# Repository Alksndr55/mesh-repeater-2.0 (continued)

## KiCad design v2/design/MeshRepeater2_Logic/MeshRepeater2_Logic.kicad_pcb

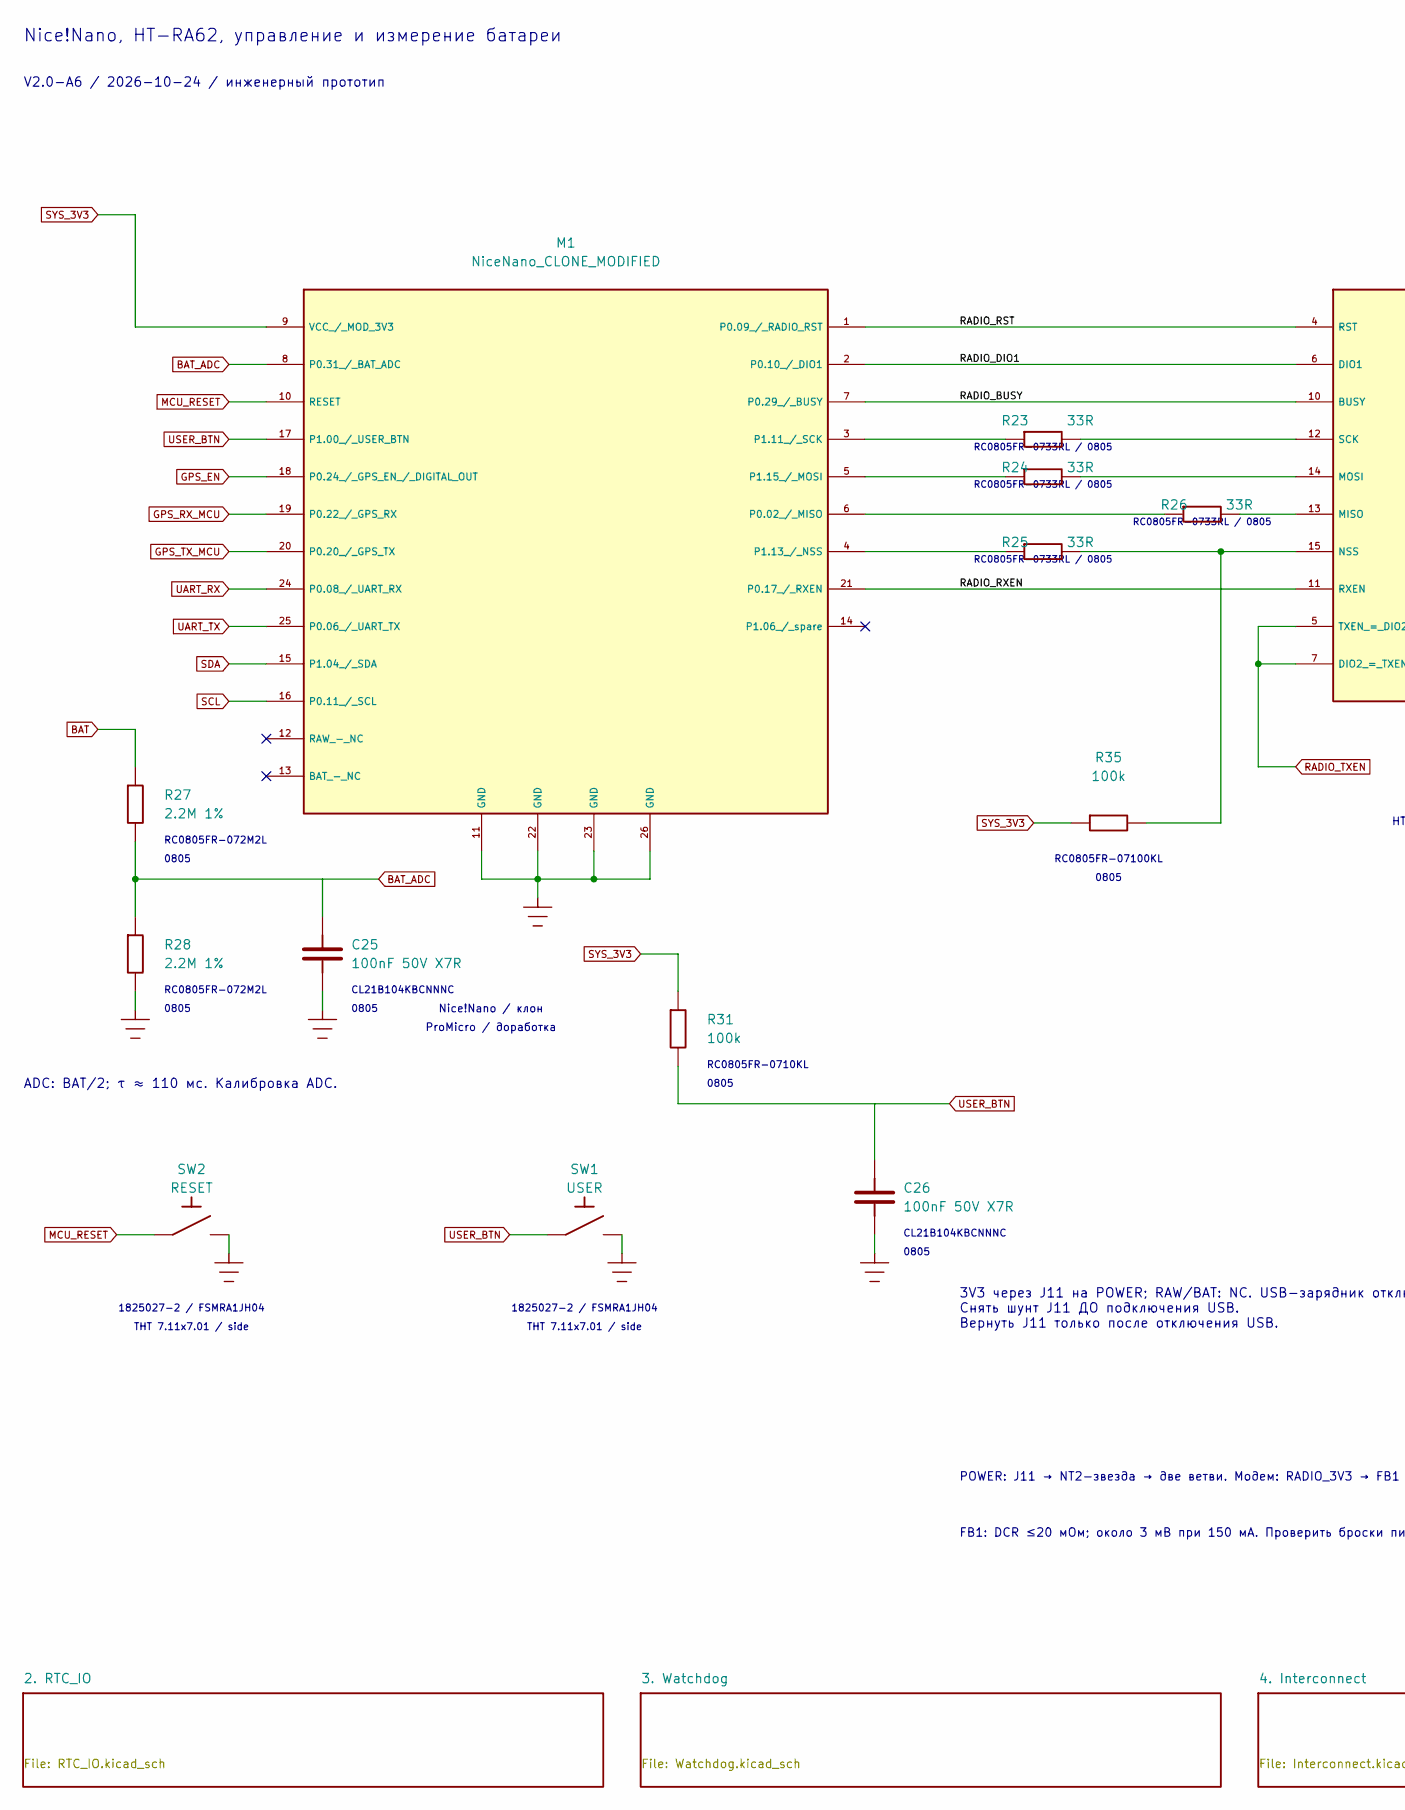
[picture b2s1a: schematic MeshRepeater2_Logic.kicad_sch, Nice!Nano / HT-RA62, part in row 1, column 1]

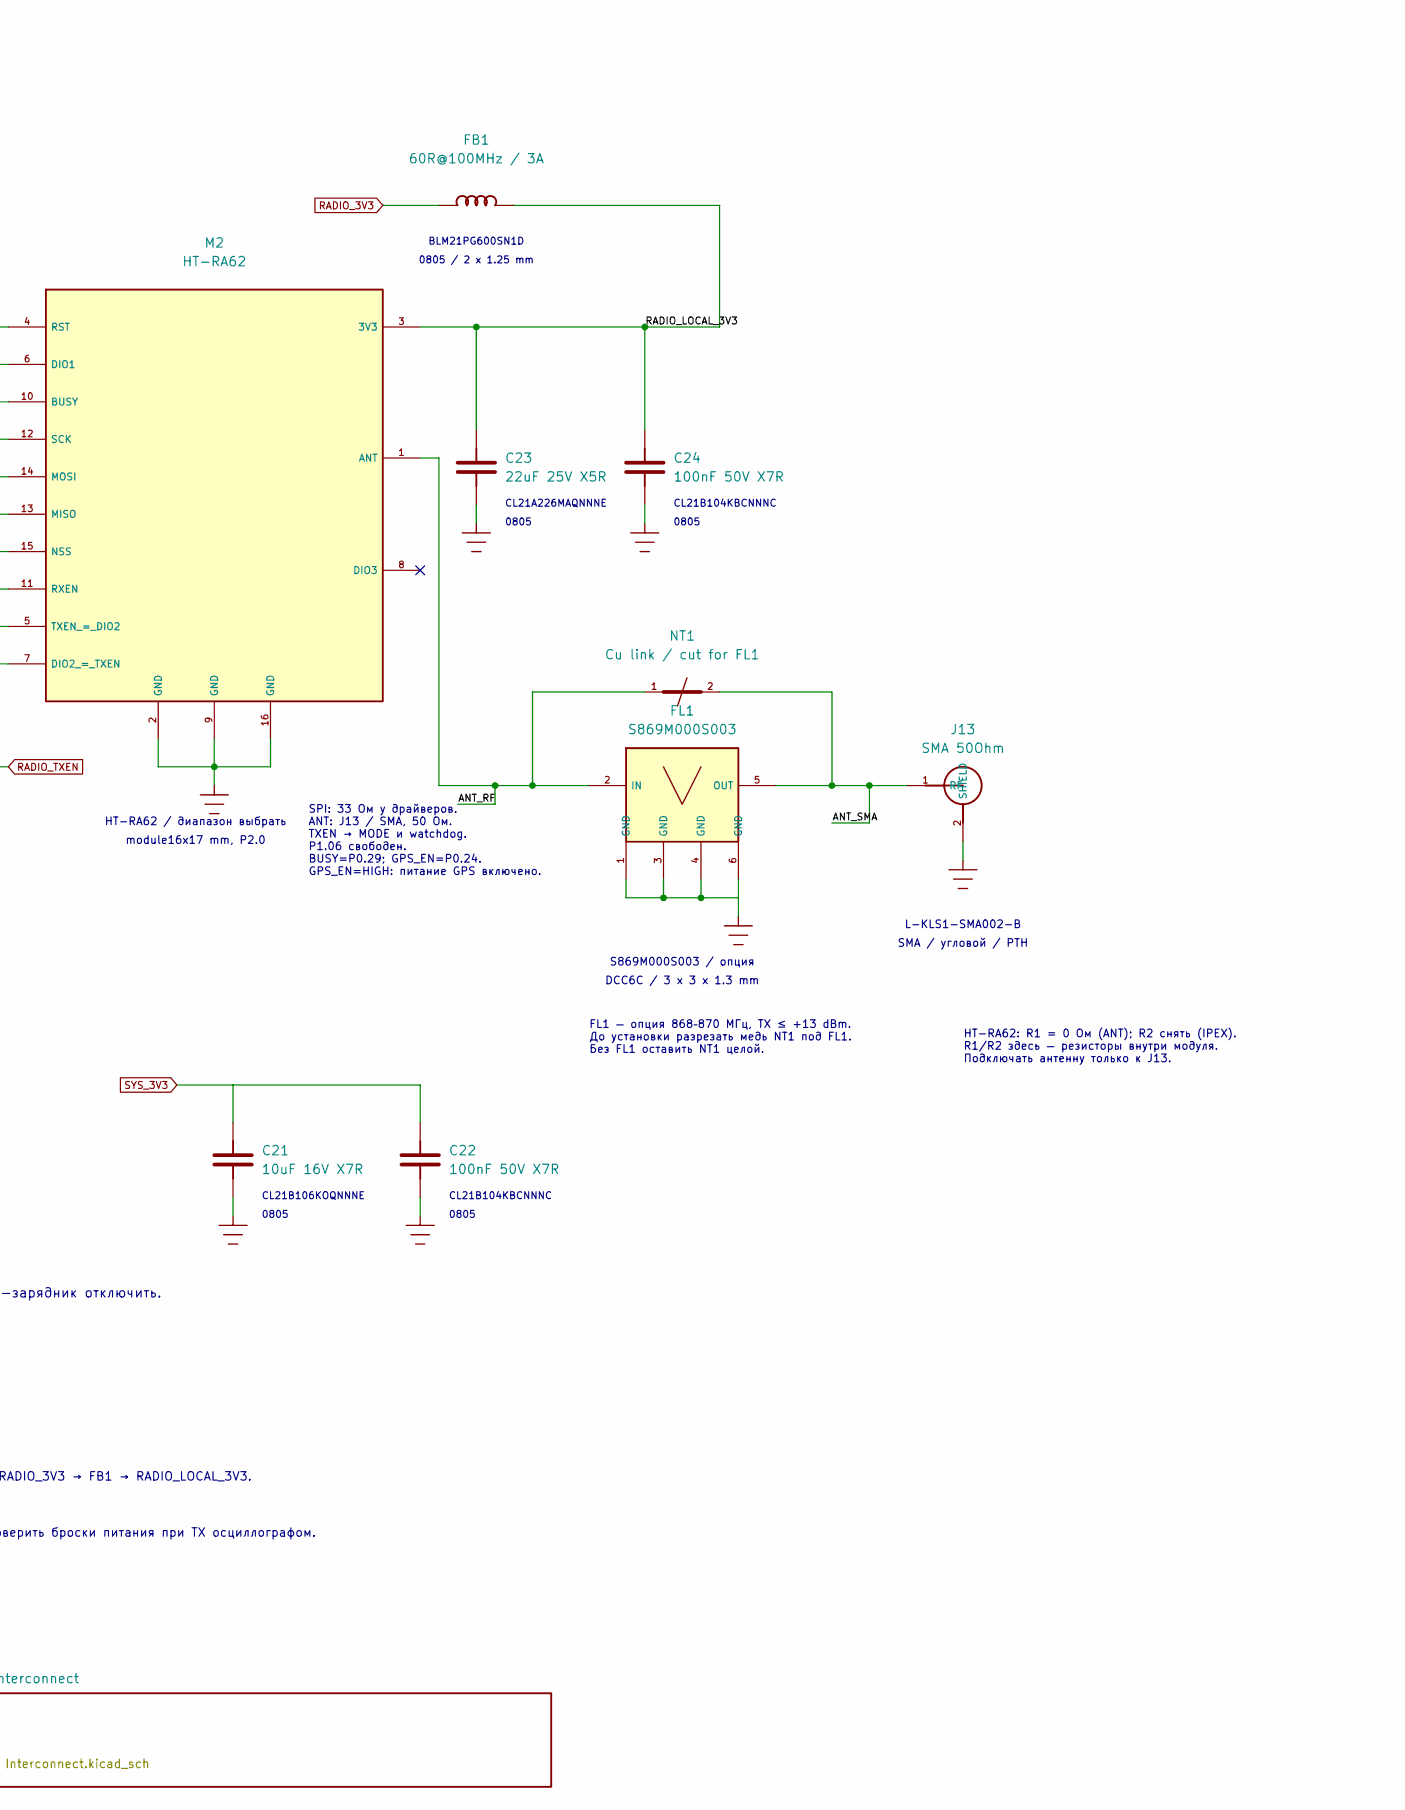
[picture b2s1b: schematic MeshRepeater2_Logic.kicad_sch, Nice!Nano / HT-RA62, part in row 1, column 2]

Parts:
C21: 10uF 16V X7R; C_0805_2012Metric__V2_C21; MPN CL21B106KOQNNNE
C22: 100nF 50V X7R; C_0805_2012Metric__V2_C22; MPN CL21B104KBCNNNC
C23: 22uF 25V X5R; C_0805_2012Metric__V2_C23; MPN CL21A226MAQNNNE
C24: 100nF 50V X7R; C_0805_2012Metric__V2_C24; MPN CL21B104KBCNNNC
C25: 100nF 50V X7R; C_0805_2012Metric__V2_C25; MPN CL21B104KBCNNNC
C26: 100nF 50V X7R; C_0805_2012Metric__V2_C26; MPN CL21B104KBCNNNC
FB1: 60R@100MHz / 3A; Ferrite_Murata_BLM21PG__V2_FB1; MPN BLM21PG600SN1D
FL1: S869M000S003; SAW_AEL_DCC6C_S869M000S003__V2_FL1; MPN S869M000S003
J13: SMA 50Ohm; SMA_KLS1_SMA002_B_Horizontal__V2_J13; MPN L-KLS1-SMA002-B
M1: NiceNano_CLONE_MODIFIED; NiceNano_13x2_Socket__V2_M1; MPN User supplied NiceNano clone
M2: HT-RA62; HT_RA62__V2_M2; MPN HT-RA62 band variant TBD
NT1: Cu link / cut for FL1; RF_Cut_Link_0p6__V2_NT1; MPN PCB copper / not purchased
R23: 33R; R_0805_2012Metric__V2_R23; MPN RC0805FR-0733RL
R24: 33R; R_0805_2012Metric__V2_R24; MPN RC0805FR-0733RL
R25: 33R; R_0805_2012Metric__V2_R25; MPN RC0805FR-0733RL
R26: 33R; R_0805_2012Metric__V2_R26; MPN RC0805FR-0733RL
R27: 2.2M 1%; R_0805_2012Metric__V2_R27; MPN RC0805FR-072M2L
R28: 2.2M 1%; R_0805_2012Metric__V2_R28; MPN RC0805FR-072M2L
R31: 100k; R_0805_2012Metric__V2_R31; MPN RC0805FR-07100KL
R35: 100k; R_0805_2012Metric__V2_R35; MPN RC0805FR-07100KL
SW1: USER; SW_TE_1825027_2_Side__V2_SW1; MPN TE1825027-2 / FSMRA1JH04
SW2: RESET; SW_TE_1825027_2_Side__V2_SW2; MPN TE1825027-2 / FSMRA1JH04

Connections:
/ANT_RF: FL1.2 (IN), M2.1 (ANT), NT1.1 (A)
/ANT_SMA: FL1.5 (OUT), J13.1 (SIGNAL), NT1.2 (B)
/RADIO_BUSY: M1.7 (P0.29_/_BUSY), M2.10 (BUSY_10)
/RADIO_DIO1: M1.2 (P0.10_/_DIO1), M2.6 (DIO1_6)
/RADIO_LOCAL_3V3: C23.1, C24.1, FB1.2, M2.3 (3V3_3)
/RADIO_RST: M1.1 (P0.09_/_RADIO_RST), M2.4 (RST_4)
/RADIO_RXEN: M1.21 (P0.17_/_RXEN), M2.11 (RXEN_11)
BAT: R27.1; also elsewhere on the board
BAT_ADC: C25.1, M1.8 (P0.31_/_BAT_ADC), R27.2, R28.1
GND: C21.2, C22.2, C23.2, C24.2, C25.2, C26.2, FL1.1 (GND), FL1.3 (GND), FL1.4 (GND), FL1.6 (GND), J13.2 (GND), M1.11 (GND), M1.22 (GND), M1.23 (GND), M1.26 (GND), M2.2 (GND_2), M2.9 (GND_9), M2.16 (GND_16), R28.2, SW1.2, SW2.2; also elsewhere on the board
GPS_EN: M1.18 (P0.24_/_GPS_EN_/_DIGITAL_OUT); also elsewhere on the board
GPS_RX_MCU: M1.19 (P0.22_/_GPS_RX); also elsewhere on the board
GPS_TX_MCU: M1.20 (P0.20_/_GPS_TX); also elsewhere on the board
MCU_RESET: M1.10 (RESET), SW2.1; also elsewhere on the board
unnamed: M1.6 (P0.02_/_MISO), R26.2
unnamed: M1.3 (P1.11_/_SCK), R23.1
unnamed: M1.4 (P1.13_/_NSS), R25.1
unnamed: M1.5 (P1.15_/_MOSI), R24.1
unnamed: M2.13 (MISO_13), R26.1
unnamed: M2.14 (MOSI_14), R24.2
unnamed: M2.15 (NSS_15), R25.2, R35.2
unnamed: M2.12 (SCK_12), R23.2
RADIO_3V3: FB1.1; also elsewhere on the board
RADIO_TXEN: M2.5 (TXEN_=_DIO2_5), M2.7 (DIO2_=_TXEN_7); also elsewhere on the board
SCL: M1.16 (P0.11_/_SCL); also elsewhere on the board
SDA: M1.15 (P1.04_/_SDA); also elsewhere on the board
SYS_3V3: C21.1, C22.1, M1.9 (VCC_/_MOD_3V3), R31.1, R35.1; also elsewhere on the board
UART_RX: M1.24 (P0.08_/_UART_RX); also elsewhere on the board
UART_TX: M1.25 (P0.06_/_UART_TX); also elsewhere on the board
USER_BTN: C26.1, M1.17 (P1.00_/_USER_BTN), R31.2, SW1.1

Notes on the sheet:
RC0805FR-0733RL / 0805
CL21B104KBCNNNC
RC0805FR-072M2L
HT-RA62 / диапазон выбрать
0805
CL21B106KOQNNNE
L-KLS1-SMA002-B
DCC6C / 3 x 3 x 1.3 mm
module16x17 mm, P2.0
ADC: BAT/2; τ ≈ 110 мс. Калибровка ADC.
1825027-2 / FSMRA1JH04
HT-RA62: R1 = 0 Ом (ANT); R2 снять (IPEX). R1/R2 здесь — резисторы внутри модуля. Подключать антенну только к J13.
V2.0-A6 / 2026-10-24 / инженерный прототип
FB1: DCR ≤20 мОм; около 3 мВ при 150 мА. Проверить броски питания при TX осциллографом.
0805 / 2 x 1.25 mm
CL21A226MAQNNNE
FL1 — опция 868–870 МГц, TX ≤ +13 dBm. До установки разрезать медь NT1 под FL1. Без FL1 оставить NT1 целой.
POWER: J11 → NT2-звезда → две ветви. Модем: RADIO_3V3 → FB1 → RADIO_LOCAL_3V3.
RC0805FR-0710KL
Nice!Nano, HT-RA62, управление и измерение батареи
ProMicro / доработка
3V3 через J11 на POWER; RAW/BAT: NC. USB-зарядник отключить. Снять шунт J11 ДО подключения USB. Вернуть J11 только после отключения USB.
THT 7.11x7.01 / side
BLM21PG600SN1D
RC0805FR-07100KL
Nice!Nano / клон
SPI: 33 Ом у драйверов. ANT: J13 / SMA, 50 Ом. TXEN → MODE и watchdog. P1.06 свободен. BUSY=P0.29; GPS_EN=P0.24. GPS_EN=HIGH: питание GPS включено.
SMA / угловой / PTH
S869M000S003 / опция

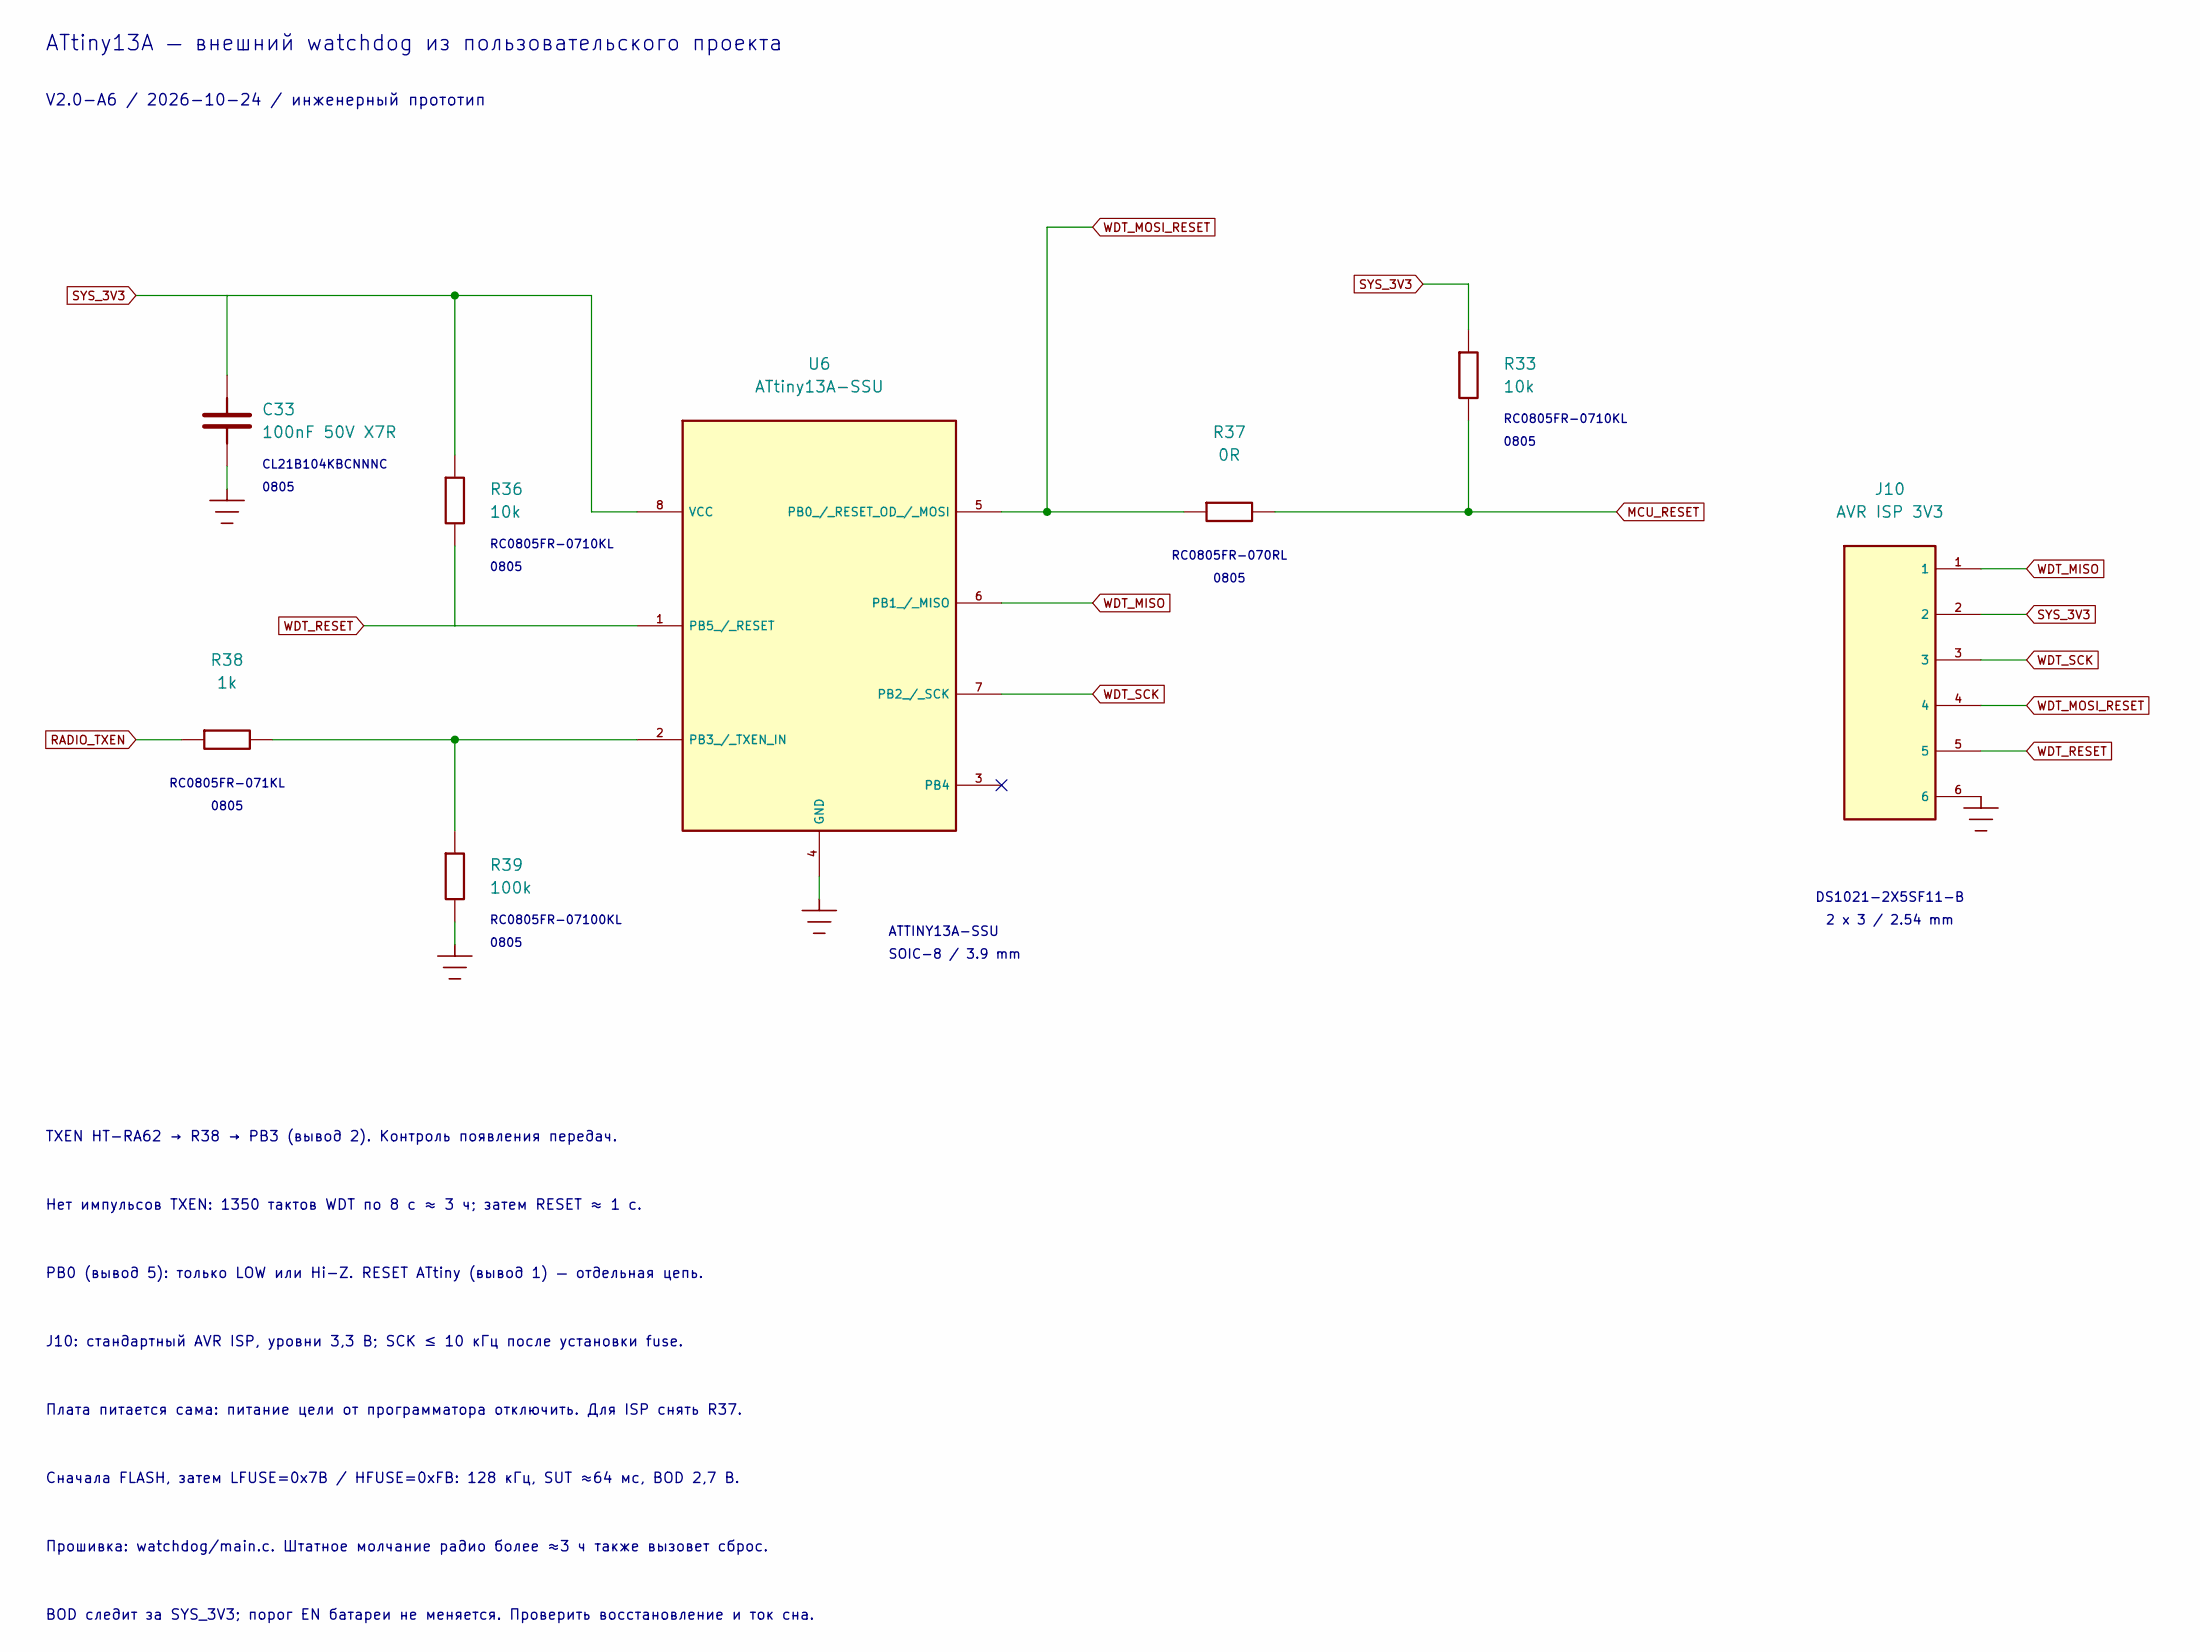
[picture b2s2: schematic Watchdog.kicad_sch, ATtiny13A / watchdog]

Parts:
C33: 100nF 50V X7R; C_0805_2012Metric__V2_C33; MPN CL21B104KBCNNNC
J10: AVR ISP 3V3; PinHeader_2x03_P2.54mm_Vertical__V2_J10; MPN DS1021-2X5SF11-B
R33: 10k; R_0805_2012Metric__V2_R33; MPN RC0805FR-0710KL
R36: 10k; R_0805_2012Metric__V2_R36; MPN RC0805FR-0710KL
R37: 0R; R_0805_2012Metric__V2_R37; MPN RC0805FR-070RL
R38: 1k; R_0805_2012Metric__V2_R38; MPN RC0805FR-071KL
R39: 100k; R_0805_2012Metric__V2_R39; MPN RC0805FR-07100KL
U6: ATtiny13A-SSU; SOIC-8_3.9x4.9mm_P1.27mm__V2_U6; MPN ATTINY13A-SSU

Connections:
GND: C33.2, J10.6, R39.2, U6.4 (GND); also elsewhere on the board
MCU_RESET: R33.2, R37.2; also elsewhere on the board
unnamed: R38.2, R39.1, U6.2 (PB3_/_TXEN_IN)
RADIO_TXEN: R38.1; also elsewhere on the board
SYS_3V3: C33.1, J10.2, R33.1, R36.1, U6.8 (VCC); also elsewhere on the board
WDT_MISO: J10.1, U6.6 (PB1_/_MISO)
WDT_MOSI_RESET: J10.4, R37.1, U6.5 (PB0_/_RESET_OD_/_MOSI)
WDT_RESET: J10.5, R36.2, U6.1 (PB5_/_RESET)
WDT_SCK: J10.3, U6.7 (PB2_/_SCK)

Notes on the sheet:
RC0805FR-070RL
J10: стандартный AVR ISP, уровни 3,3 В; SCK ≤ 10 кГц после установки fuse.
0805
RC0805FR-071KL
ATTINY13A-SSU
TXEN HT-RA62 → R38 → PB3 (вывод 2). Контроль появления передач.
2 x 3 / 2.54 mm
SOIC-8 / 3.9 mm
Плата питается сама: питание цели от программатора отключить. Для ISP снять R37.
RC0805FR-0710KL
Сначала FLASH, затем LFUSE=0x7B / HFUSE=0xFB: 128 кГц, SUT ≈64 мс, BOD 2,7 В.
PB0 (вывод 5): только LOW или Hi-Z. RESET ATtiny (вывод 1) — отдельная цепь.
CL21B104KBCNNNC
DS1021-2X5SF11-B
V2.0-A6 / 2026-10-24 / инженерный прототип
BOD следит за SYS_3V3; порог EN батареи не меняется. Проверить восстановление и ток сна.
Прошивка: watchdog/main.c. Штатное молчание радио более ≈3 ч также вызовет сброс.
ATtiny13A — внешний watchdog из пользовательского проекта
RC0805FR-07100KL
Нет импульсов TXEN: 1350 тактов WDT по 8 с ≈ 3 ч; затем RESET ≈ 1 с.

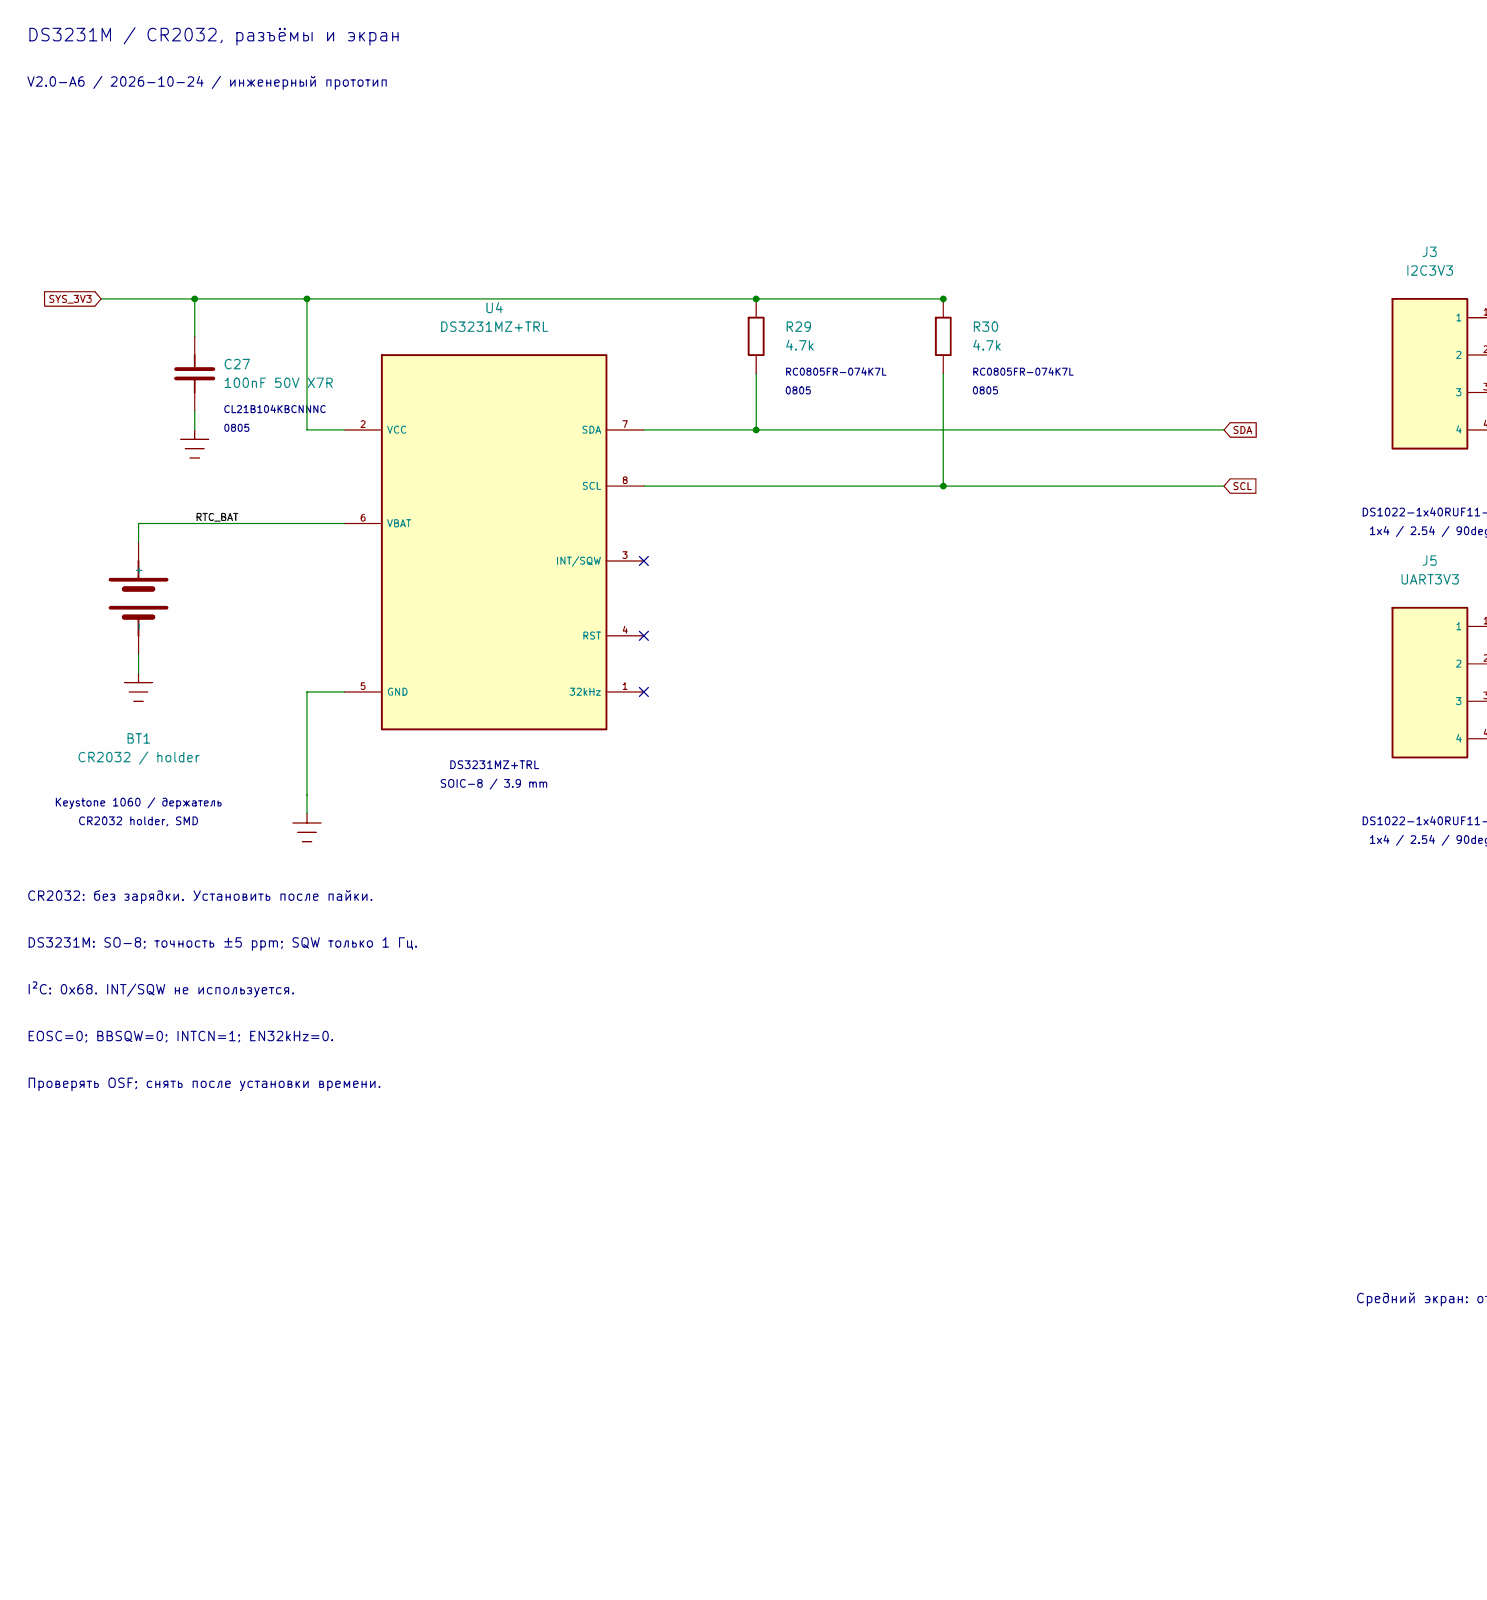
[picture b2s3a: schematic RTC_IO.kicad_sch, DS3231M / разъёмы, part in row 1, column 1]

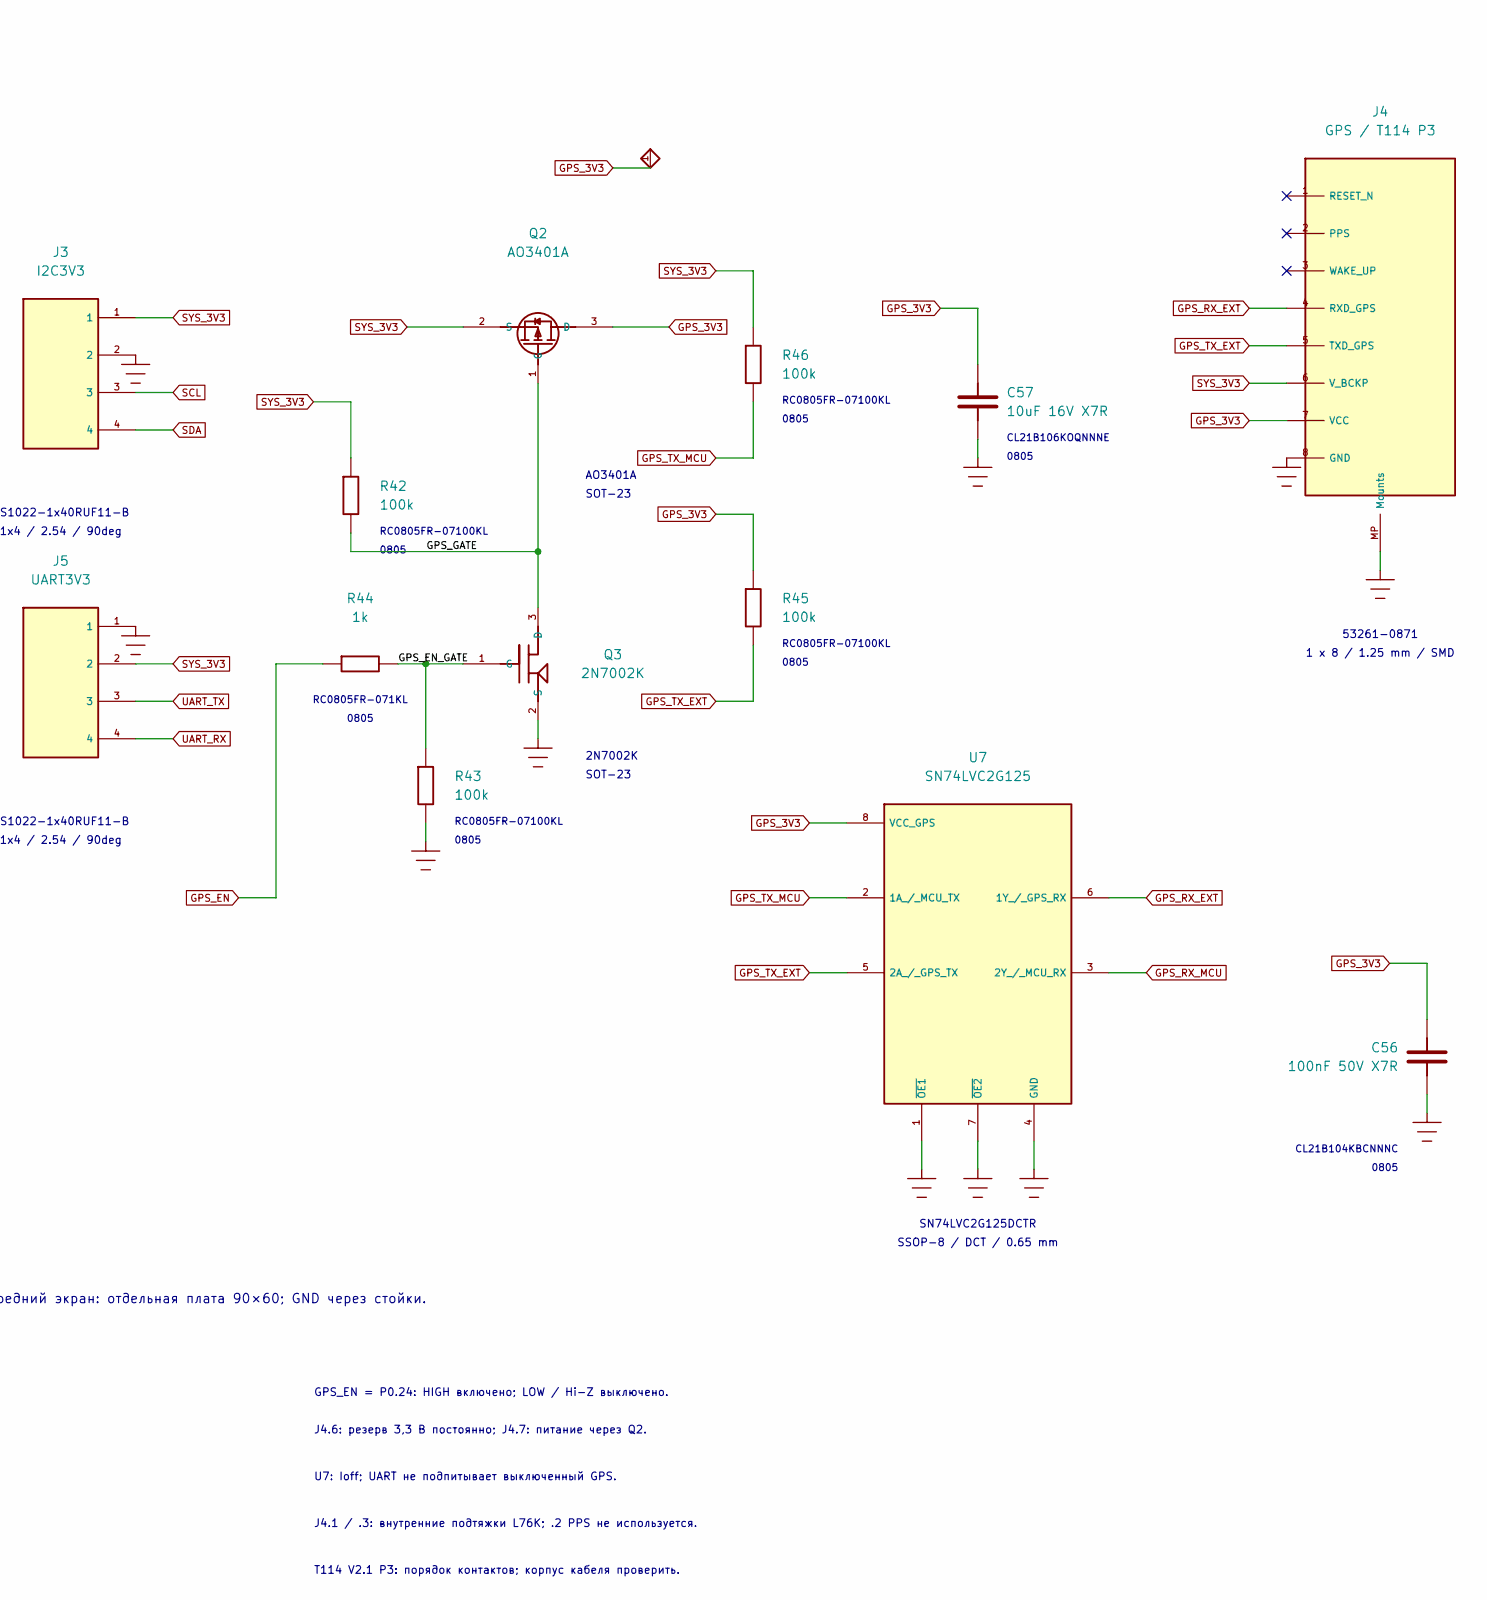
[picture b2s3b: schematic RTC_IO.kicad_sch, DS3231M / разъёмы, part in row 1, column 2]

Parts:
BT1: CR2032 / holder; BatteryHolder_Keystone_1060_1x2032__V2_BT1; MPN 1060; LCSC C5370859
C27: 100nF 50V X7R; C_0805_2012Metric__V2_C27; MPN CL21B104KBCNNNC
C56: 100nF 50V X7R; C_0805_2012Metric__V2_C56; MPN CL21B104KBCNNNC
C57: 10uF 16V X7R; C_0805_2012Metric__V2_C57; MPN CL21B106KOQNNNE
J3: I2C3V3; Connfly_DS1022_1x04RUF11_B_Horizontal__V2_J3; MPN DS1022-1x40RUF11-B cut to4pins
J4: GPS / T114 P3; Molex_PicoBlade_53261-0871_1x08-1MP_P1.25mm_Horizontal__V2_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; MPN 53261-0871
J5: UART3V3; Connfly_DS1022_1x04RUF11_B_Horizontal__V2_J5; MPN DS1022-1x40RUF11-B cut to4pins
Q2: AO3401A; SOT-23__V2_Q2; MPN AO3401A
Q3: 2N7002K; SOT-23__V2_Q3; MPN 2N7002K
R29: 4.7k; R_0805_2012Metric__V2_R29; MPN RC0805FR-074K7L
R30: 4.7k; R_0805_2012Metric__V2_R30; MPN RC0805FR-074K7L
R42: 100k; R_0805_2012Metric__V2_R42; MPN RC0805FR-07100KL
R43: 100k; R_0805_2012Metric__V2_R43; MPN RC0805FR-07100KL
R44: 1k; R_0805_2012Metric__V2_R44; MPN RC0805FR-071KL
R45: 100k; R_0805_2012Metric__V2_R45; MPN RC0805FR-07100KL
R46: 100k; R_0805_2012Metric__V2_R46; MPN RC0805FR-07100KL
U4: DS3231MZ+TRL; SOIC-8_3.9x4.9mm_P1.27mm__V2_U4; MPN DS3231MZ+TRL
U7: SN74LVC2G125; TI_DCT0008A__V2_U7; MPN SN74LVC2G125DCTR

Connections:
/2. RTC_IO/GPS_EN_GATE: Q3.1 (G), R43.1, R44.2
/2. RTC_IO/GPS_GATE: Q2.1 (G), Q3.3 (D), R42.2
/2. RTC_IO/RTC_BAT: BT1.1 (+), U4.6 (VBAT)
GND: BT1.2 (-), C27.2, C56.2, C57.2, J3.2, J4.8 (GND), J4.MP (Mounts), J5.1, Q3.2 (S), R43.2, U4.5 (GND), U7.1 (~OE1), U7.4 (GND), U7.7 (~OE2); also elsewhere on the board
GPS_3V3: C56.1, C57.1, J4.7 (VCC), Q2.3 (D), R45.1, U7.8 (VCC_GPS)
GPS_EN: R44.1; also elsewhere on the board
GPS_RX_EXT: J4.4 (RXD_GPS), U7.6 (1Y_/_GPS_RX)
GPS_RX_MCU: U7.3 (2Y_/_MCU_RX); also elsewhere on the board
GPS_TX_EXT: J4.5 (TXD_GPS), R45.2, U7.5 (2A_/_GPS_TX)
GPS_TX_MCU: R46.2, U7.2 (1A_/_MCU_TX); also elsewhere on the board
SCL: J3.3, R30.2, U4.8 (SCL); also elsewhere on the board
SDA: J3.4, R29.2, U4.7 (SDA); also elsewhere on the board
SYS_3V3: C27.1, J3.1, J4.6 (V_BCKP), J5.2, Q2.2 (S), R29.1, R30.1, R42.1, R46.1, U4.2 (VCC); also elsewhere on the board
UART_RX: J5.4; also elsewhere on the board
UART_TX: J5.3; also elsewhere on the board

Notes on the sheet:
J4.6: резерв 3,3 В постоянно; J4.7: питание через Q2.
2N7002K
1x4 / 2.54 / 90deg
CL21B104KBCNNNC
J4.1 / .3: внутренние подтяжки L76K; .2 PPS не используется.
0805
U7: Ioff; UART не подпитывает выключенный GPS.
V2.0-A6 / 2026-10-24 / инженерный прототип
EOSC=0; BBSQW=0; INTCN=1; EN32kHz=0.
DS3231MZ+TRL
RC0805FR-07100KL
Проверять OSF; снять после установки времени.
Keystone 1060 / держатель
RC0805FR-074K7L
T114 V2.1 P3: порядок контактов; корпус кабеля проверить.
Средний экран: отдельная плата 90×60; GND через стойки.
RC0805FR-071KL
DS1022-1x40RUF11-B
53261-0871
DS3231M: SO-8; точность ±5 ppm; SQW только 1 Гц.
SN74LVC2G125DCTR
SOT-23
I²C: 0x68. INT/SQW не используется.
GPS_EN = P0.24: HIGH включено; LOW / Hi-Z выключено.
CR2032: без зарядки. Установить после пайки.
1 x 8 / 1.25 mm / SMD
CR2032 holder, SMD
AO3401A
CL21B106KOQNNNE
SSOP-8 / DCT / 0.65 mm
SOIC-8 / 3.9 mm
DS3231M / CR2032, разъёмы и экран
